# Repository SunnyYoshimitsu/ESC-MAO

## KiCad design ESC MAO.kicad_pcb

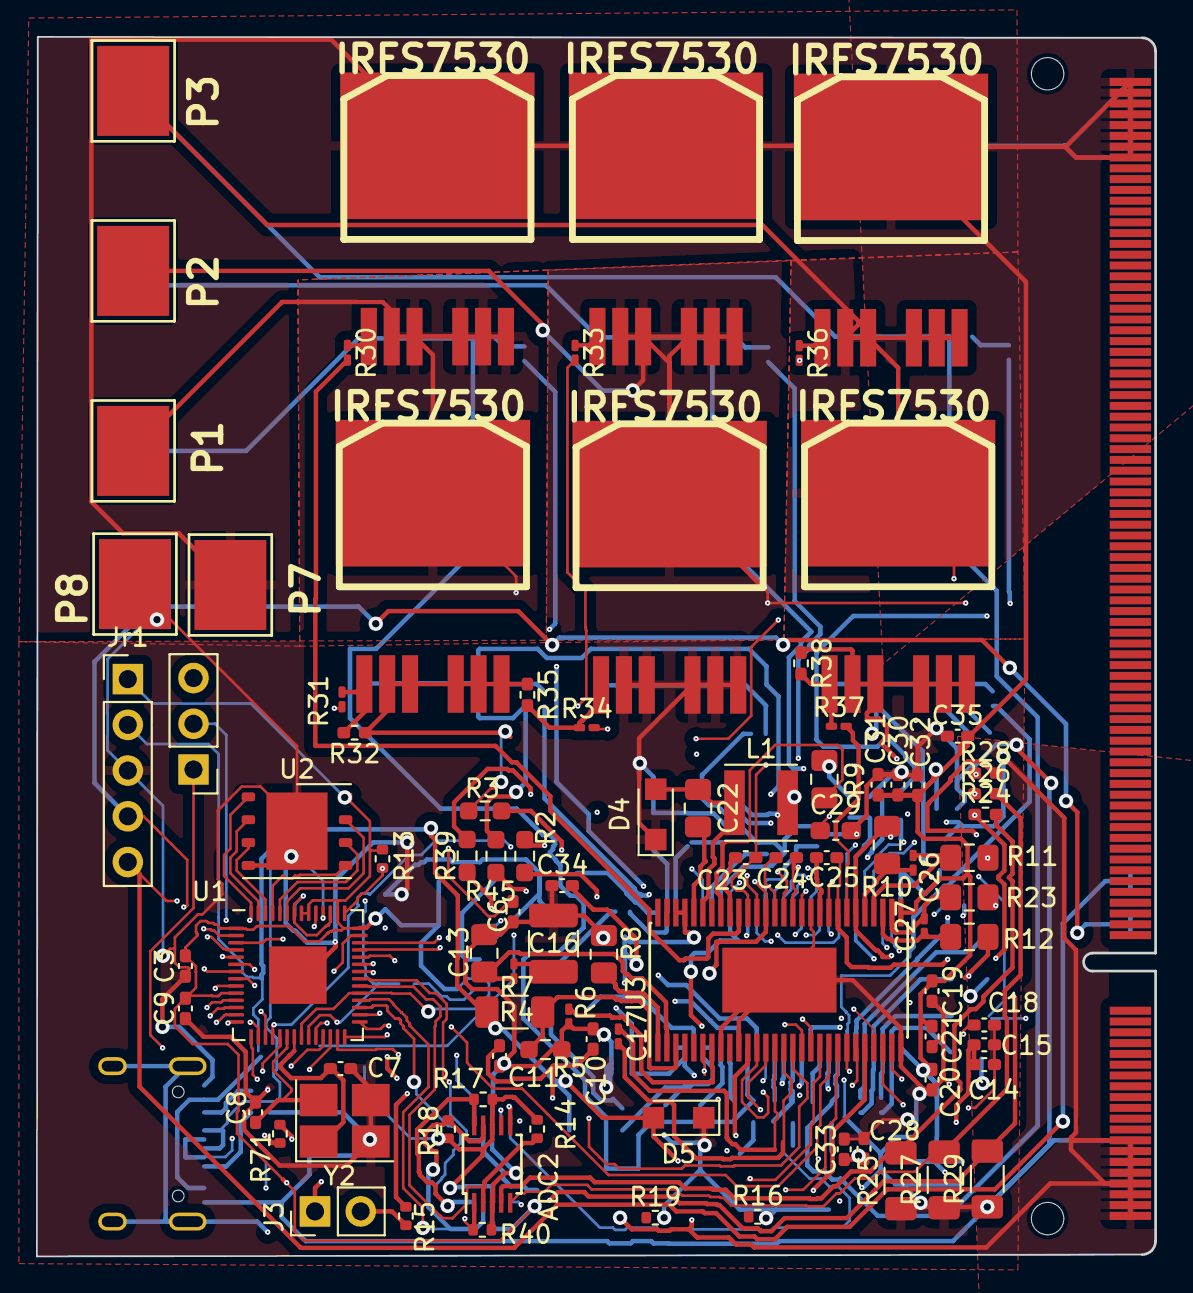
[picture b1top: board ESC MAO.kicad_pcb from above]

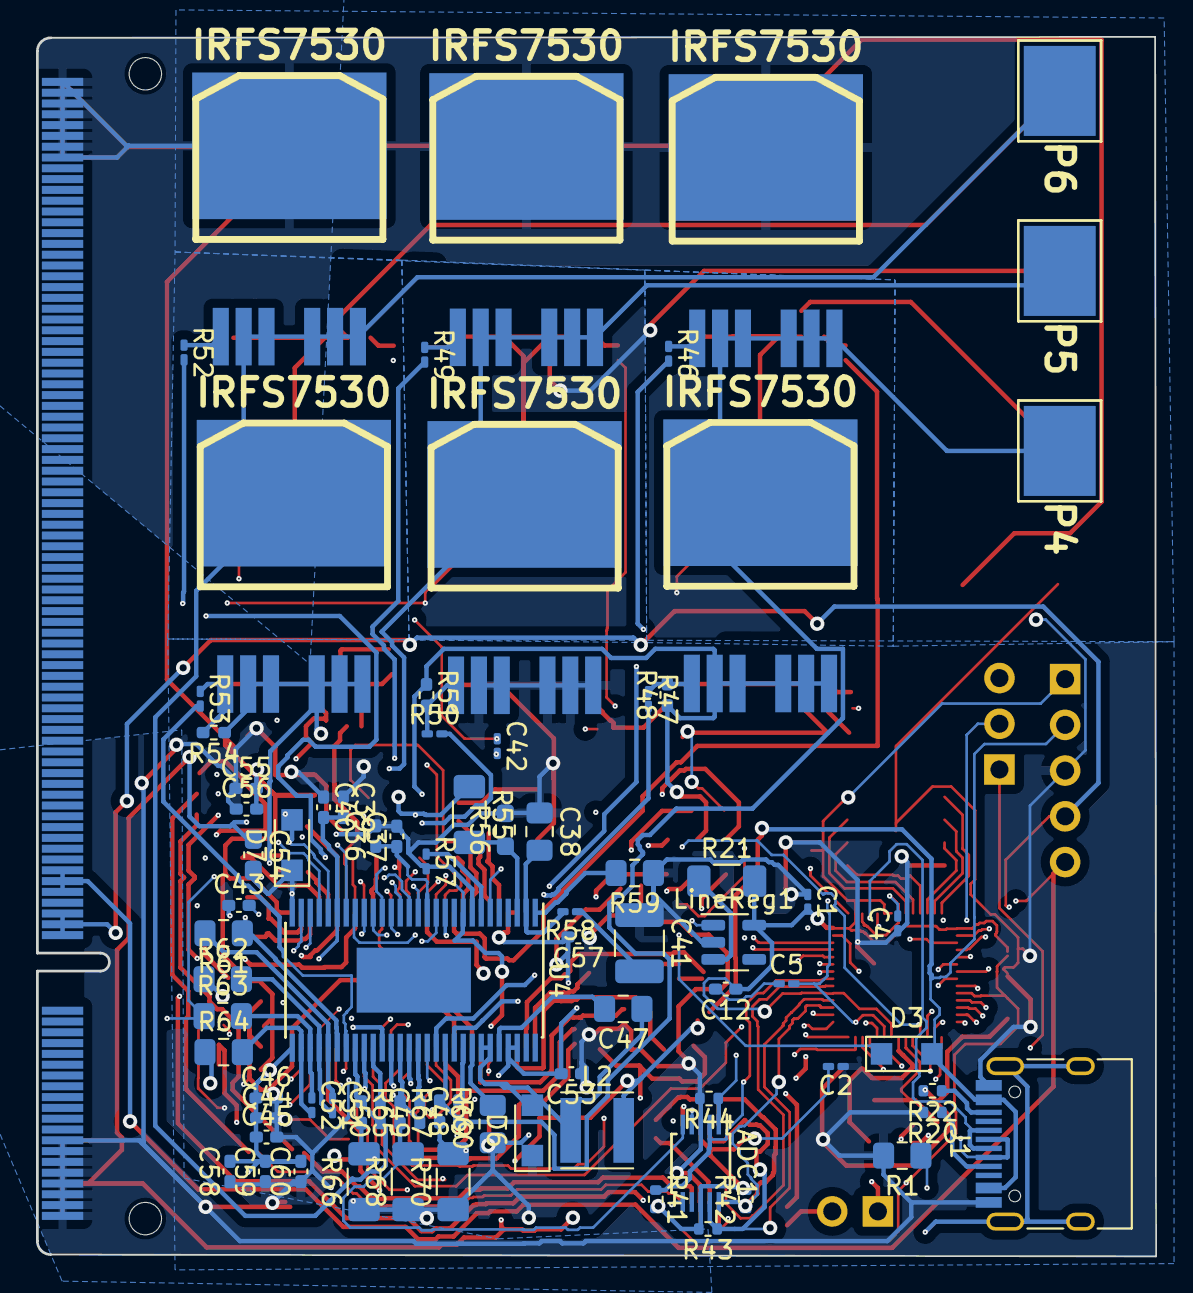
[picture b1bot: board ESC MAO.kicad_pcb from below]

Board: 4 copper layers, 62.1 x 67.8 mm, 171 parts (80 on the bottom side), 140 nets.

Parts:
ADC1, ADC2: ADS1015IDGS; TSSOP-10_3x3mm_P0.5mm
C1, C2, C4, C5: 100nF; C_0201_0603Metric_Pad0.64x0.40mm_HandSolder
C3, C6: 2.2uF; C_0402_1005Metric_Pad0.74x0.62mm_HandSolder
C7, C8: 15pF; C_0402_1005Metric_Pad0.74x0.62mm_HandSolder
C9, C12: 10uF; C_0402_1005Metric_Pad0.74x0.62mm_HandSolder
C10, C11, C14, C15, C18, C36, C37, C39, C40, C43: 2.2u; C_0402_1005Metric_Pad0.74x0.62mm_HandSolder
C13, C38: 120p; C_0805_2012Metric_Pad1.18x1.45mm_HandSolder
C16, C41: 6.8n; C_1210_3225Metric_Pad1.33x2.70mm_HandSolder
C17, C42: 22n; C_0201_0603Metric_Pad0.64x0.40mm_HandSolder
C19, C20, C21, C28, C30, C31, C33, C34, C44, C45, C46, C53, C55, C56, C58, C59: 10u,50V; C_0402_1005Metric_Pad0.74x0.62mm_HandSolder
C22, C47: 100n; C_0805_2012Metric_Pad1.18x1.45mm_HandSolder
C23, C24, C25, C48, C49, C50: 220n; C_0402_1005Metric_Pad0.74x0.62mm_HandSolder
C26, C27, C51, C52: 2.2n; C_0201_0603Metric_Pad0.64x0.40mm_HandSolder
C29, C54: 100u; C_0603_1608Metric_Pad1.08x0.95mm_HandSolder
C32, C57: 15u, 100v; C_0402_1005Metric_Pad0.74x0.62mm_HandSolder
C35, C60: 15u,100V; C_0402_1005Metric_Pad0.74x0.62mm_HandSolder
D3: MBR120VLSFT1G; Nexperia_CFP3_SOD-123W
D4, D6: DIODESCH; Nexperia_CFP3_SOD-123W
D5, D7: TVS 5V; Nexperia_CFP3_SOD-123W
J1: USB_C_Receptacle_USB2.0; USB_C_Receptacle_HRO_TYPE-C-31-M-12
J2: Conn_01x03_Pin; PinHeader_1x03_P2.54mm_Vertical
J3: Conn_01x02_Pin; PinHeader_1x02_P2.54mm_Vertical
Jr1: Conn_01x05_Pin; PinHeader_1x05_P2.54mm_Vertical
L1, L2: 22u; L_Vishay_IFSC-1515AH_4x4x1.8mm
LineReg1: TLV75733PDBV; SOT-23-5
P1, P4: MOTOR3; 1PAD_4x5mm
P2, P5: MOTOR2; 1PAD_4x5mm
P3, P6: MOTOR1; 1PAD_4x5mm
P7: IN+; 1PAD_4x5mm
P8: IN-; 1PAD_4x5mm
Q1, Q2, Q3, Q4, Q5, Q6, Q7, Q8, Q9, Q10, Q11, Q12: IRFS7530; D2PAK-7-GDS
R1, R9, R60: 1M; C_0805_2012Metric_Pad1.18x1.45mm_HandSolder
R2, R3, R39, R45: SHUNT; R_0603_1608Metric_Pad0.98x0.95mm_HandSolder
R4, R55: 18k; R_1206_3216Metric_Pad1.30x1.75mm_HandSolder
R5, R56: 3k3; R_0603_1608Metric_Pad0.98x0.95mm_HandSolder
R6, R57: 10k; R_0201_0603Metric_Pad0.64x0.40mm_HandSolder
R7, R58: 15k; R_0201_0603Metric_Pad0.64x0.40mm_HandSolder
R8, R59: 220k; C_0805_2012Metric_Pad1.18x1.45mm_HandSolder
R10, R11, R12, R23, R61, R62, R63, R64: 100R; C_0805_2012Metric_Pad1.18x1.45mm_HandSolder
R13, R14, R15, R17, R18, R20, R22, R40, R41, R42, R43, R44, R71: 5k; R_0402_1005Metric
R16, R19: 47.5k; R_0402_1005Metric
R21: 100k; R_1206_3216Metric_Pad1.30x1.75mm_HandSolder
R24, R26, R28, R32, R35, R38, R48, R51, R54, R65, R67, R69: 39k; R_0402_1005Metric_Pad0.72x0.64mm_HandSolder
R25, R27, R29, R66, R68, R70: 2k2; R_1206_3216Metric_Pad1.30x1.75mm_HandSolder
R30, R31, R33, R34, R36, R37, R46, R47, R49, R50, R52, R53: 4R7; R_0201_0603Metric_Pad0.64x0.40mm_HandSolder
SODIMM DDR2: SODIMM DDR2 EDGE; SODIMM_DDR2_EDGE
U1: RP2040; QFN-56-1EP_7x7mm_P0.4mm_EP3.2x3.2mm
U2: W25Q32JVZP; WSON-8-1EP_6x5mm_P1.27mm_EP3.4x4.3mm
U3, U4: DRV8302; HTSSOP-56-1EP_6.1x14mm_P0.5mm_EP3.61x6.35mm
Y2: 12MHz; Crystal_SMD_3225-4Pin_3.2x2.5mm_HandSoldering

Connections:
1BR_SO1: U1.38 (GPIO26_ADC0), U4.25 (SO1)
1BR_SO2: U1.39 (GPIO27_ADC1), U4.26 (SO2)
1DC_CAL: U1.15 (GPIO12), U4.12 (DC_CAL)
1H1: U1.17 (GPIO14), U4.17 (INH_A)
1H2: U1.27 (GPIO16), U4.19 (INH_B)
1H3: U1.29 (GPIO18), U4.21 (INH_C)
1L1: U1.18 (GPIO15), U4.18 (INL_A)
1L2: U1.28 (GPIO17), U4.20 (INL_B)
1L3: U1.30 (GPIO19), U4.22 (INL_C)
1SENS1: ADC1.4 (AIN0), R65.2, R66.2
1SENS2: ADC1.5 (AIN1), R67.2, R68.2
1SENS3: ADC1.6 (AIN2), R69.2, R70.2
+1V1: C4.2, C5.2, U1.23 (DVDD), U1.45 (VREG_VOUT), U1.50 (DVDD)
+3V3: ADC1.8 (VDD), ADC2.8 (VDD), C1.2, C2.2, C3.2, C9.2, C12.1, Jr1.1, LineReg1.5 (OUT), R13.2, R14.2, R17.2, R18.2, R21.2, R41.2, R42.2, R43.2, R71.2, U1.1 (IOVDD), U1.10 (IOVDD), U1.22 (IOVDD), U1.33 (IOVDD), U1.42 (IOVDD), U1.44 (VREG_IN), U1.48 (USB_VDD), U1.49 (IOVDD), U2.8 (VCC)
+5V: C29.1, C54.1, D3.2 (A), D5.2 (K), D7.2 (K), J1.A4 (VBUS), J1.A9 (VBUS), J1.B4 (VBUS), J1.B9 (VBUS), Jr1.2, L1.2, L2.2, R4.1, R55.1, SODIMM DDR2.1, SODIMM DDR2.3, SODIMM DDR2.5, SODIMM DDR2.9, SODIMM DDR2.11, SODIMM DDR2.13, SODIMM DDR2.15, SODIMM DDR2.e, U3.9 (M_OC), U3.24 (REF), U4.9 (M_OC), U4.24 (REF)
/MosfetDr1/H1_LOW: Q8.S, R45.2, R48.1, R51.1, R63.1, U4.44 (SL_A)
/MosfetDr1/H1_VS: C48.1, P4.1, Q7.S, Q8.D, R69.1, U4.46 (SH_A)
/MosfetDr1/H2_VS: C49.1, P5.1, Q9.S, Q10.D, R67.1, U4.41 (SH_B)
/MosfetDr1/H3_LOW: Q12.S, R39.1, R54.1, R61.1, U4.34 (SL_C)
/MosfetDr1/H3_VS: C50.1, P6.1, Q11.S, Q12.D, R65.1, U4.36 (SH_C)
/MosfetDr1/M_H1: R46.2, U4.47 (GH_A)
/MosfetDr1/M_H2: R49.2, U4.42 (GH_B)
/MosfetDr1/M_H3: R52.2, U4.37 (GH_C)
/MosfetDr1/M_L1: R47.2, U4.45 (GL_A)
/MosfetDr1/M_L2: R50.2, U4.40 (GL_B)
/MosfetDr1/M_L3: R53.2, U4.35 (GL_C)
/MosfetDr/H1_LOW: Q2.S, R3.2, R12.1, R32.1, R35.1, U3.44 (SL_A)
/MosfetDr/H1_VS: C23.1, P1.1, Q1.S, Q2.D, R28.1, U3.46 (SH_A)
/MosfetDr/H2_VS: C24.1, P2.1, Q3.S, Q4.D, R26.1, U3.41 (SH_B)
/MosfetDr/H3_LOW: Q6.S, R2.1, R10.1, R38.1, U3.34 (SL_C)
/MosfetDr/H3_VS: C25.1, P3.1, Q5.S, Q6.D, R24.1, U3.36 (SH_C)
/MosfetDr/M_H1: R30.2, U3.47 (GH_A)
/MosfetDr/M_H2: R33.2, U3.42 (GH_B)
/MosfetDr/M_H3: R36.2, U3.37 (GH_C)
/MosfetDr/M_L1: R31.2, U3.45 (GL_A)
/MosfetDr/M_L2: R34.2, U3.40 (GL_B)
/MosfetDr/M_L3: R37.2, U3.35 (GL_C)
/PowerMana1/SH1_B: R39.2, R62.1
/PowerMana1/SH2_B: R45.1, R64.1
/PowerMana/SH1_B: R2.2, R11.1
/PowerMana/SH2_B: R3.1, R23.1
ADCs0: ADC2.1 (ADDR), R40.1, U1.12 (GPIO9)
ADCs1: ADC1.1 (ADDR), R44.1, U1.13 (GPIO10)
BR_SO1: U1.40 (GPIO28_ADC2), U3.25 (SO1)
BR_SO2: U1.41 (GPIO29_ADC3), U3.26 (SO2)
DC_CAL: U1.3 (GPIO1), U3.12 (DC_CAL)
En_GATE: U1.4 (GPIO2), U3.16 (EN_GATE)
En_GATE1: U1.16 (GPIO13), U4.16 (EN_GATE)
GND: ADC1.3 (GND), ADC2.3 (GND), C1.1, C2.1, C3.1, C4.1, C5.1, C6.1, C7.1, C8.1, C9.1, C10.2, C11.2, C12.2, C13.1, C14.1, C15.1, C16.1, C18.1, C19.2, C20.2, C21.2, C28.1, C29.2, C30.1, C31.1, C32.1, C33.1, C34.1, C35.1, C36.2, C37.2, C38.1, C39.1, C40.1, C41.1, C43.1, C44.2, C45.2, C46.2, C53.1, C54.2, C55.1, C56.1, C57.1, C58.1, C59.1, C60.1, D4.1 (A), D5.1 (A), D6.1 (A), D7.1 (A), J1.A1 (GND), J1.A12 (GND), J1.B1 (GND), J1.B12 (GND), Jr1.3, LineReg1.2 (GND), P8.1, Q4.S, Q10.S, R1.2, R5.2, R6.2, R8.1, R9.1, R16.2, R19.2, R20.2, R22.2, R25.1, R27.1, R29.1, R40.2, R44.2, R56.2, R57.2, R59.1, R60.1, R66.1, R68.1, R70.1, SODIMM DDR2.2, SODIMM DDR2.4, SODIMM DDR2.6, SODIMM DDR2.8, SODIMM DDR2.10, SODIMM DDR2.12, SODIMM DDR2.14, SODIMM DDR2.16, U1.57 (GND), U2.4 (GND), U2.9 (EP), U3.8 (M_PWM), U3.10 (GAIN), U3.28 (AGND), U3.39 (SL_B), U3.57 (GND(POWER_PAD)), U4.8 (M_PWM), U4.10 (GAIN), U4.28 (AGND), U4.39 (SL_B), U4.57 (GND(POWER_PAD)), Y2.2, Y2.3
H1: U1.5 (GPIO3), U3.17 (INH_A)
H2: U1.7 (GPIO5), U3.19 (INH_B)
H3: U1.9 (GPIO7), U3.21 (INH_C)
K7: LineReg1.3 (EN), R21.1
L1: U1.6 (GPIO4), U3.18 (INL_A)
L2: U1.8 (GPIO6), U3.20 (INL_B)
L3: U1.11 (GPIO8), U3.22 (INL_C)
unnamed: C16.2, R7.1
unnamed: C41.2, R58.1
unnamed: C22.1, D4.2 (K), L1.1, U3.50 (PH), U3.51 (PH)
unnamed: C47.1, D6.2 (K), L2.1, U4.50 (PH), U4.51 (PH)
unnamed: J1.A5 (CC1), R20.1
unnamed: J1.B5 (CC2), R22.1
unnamed: J1.S1 (SHIELD), R1.1
unnamed: J2.1, U1.25 (SWD)
unnamed: J2.2, U1.24 (SWCLK)
unnamed: J2.3, U1.19 (TESTEN)
unnamed: J3.1, R71.1, U1.26 (RUN)
unnamed: J3.2, R15.1
unnamed: Q1.G, R30.1
unnamed: Q2.G, R31.1, R32.2
unnamed: Q3.G, R33.1
unnamed: Q4.G, R34.1, R35.2
unnamed: Q5.G, R36.1
unnamed: Q6.G, R37.1, R38.2
unnamed: Q7.G, R46.1
unnamed: Q8.G, R47.1, R48.2
unnamed: Q9.G, R49.1
unnamed: Q10.G, R50.1, R51.2
unnamed: Q11.G, R52.1
unnamed: Q12.G, R53.1, R54.2
unnamed: C6.2, R13.1, U1.43 (ADC_AVDD)
unnamed: U1.52 (QSPI_SCLK), U2.6 (CLK)
unnamed: U1.53 (QSPI_SD0), U2.5 (DI(IO0))
unnamed: U1.55 (QSPI_SD1), U2.2 (DO(IO1))
unnamed: U1.54 (QSPI_SD2), U2.3 (IO2)
unnamed: U1.51 (QSPI_SD3), U2.7 (IO3)
unnamed: R15.2, U1.56 (QSPI_SS), U2.1 (~CS)
unnamed: J1.A6 (D+), J1.B6 (D+), U1.46 (USB_DM)
unnamed: J1.A7 (D-), J1.B7 (D-), U1.47 (USB_DP)
unnamed: C8.2, U1.20 (XIN), Y2.4
unnamed: C7.2, U1.21 (XOUT), Y2.1
unnamed: C18.2, U3.27 (AVDD)
unnamed: R9.2, U3.49 (BIAS)
unnamed: C23.2, U3.48 (BST_A)
unnamed: C24.2, U3.43 (BST_B)
unnamed: C22.2, U3.52 (BST_BK)
unnamed: C25.2, U3.38 (BST_C)
unnamed: C13.2, R7.2, U3.2 (COMP)
unnamed: C17.1, U3.14 (CP1)
unnamed: C17.2, U3.15 (CP2)
unnamed: R6.1, U3.7 (DTC)
unnamed: C14.2, C15.2, U3.11 (OC_ADJ), U3.23 (DVDD)
unnamed: C10.1, C11.1, U3.13 (GVDD)
unnamed: R8.2, U3.1 (RT_CLK)
unnamed: C26.1, R10.2, U3.33 (SN1)
unnamed: C27.1, R12.2, U3.31 (SN2)
unnamed: C26.2, R11.2, U3.32 (SP1)
unnamed: C27.2, R23.2, U3.30 (SP2)
unnamed: R4.2, R5.1, U3.3 (VSENSE)
unnamed: C43.2, U4.27 (AVDD)
unnamed: R60.2, U4.49 (BIAS)
unnamed: C48.2, U4.48 (BST_A)
unnamed: C49.2, U4.43 (BST_B)
unnamed: C47.2, U4.52 (BST_BK)
unnamed: C50.2, U4.38 (BST_C)
unnamed: C38.2, R58.2, U4.2 (COMP)
unnamed: C42.1, U4.14 (CP1)
unnamed: C42.2, U4.15 (CP2)
unnamed: R57.1, U4.7 (DTC)
unnamed: C39.2, C40.2, U4.11 (OC_ADJ), U4.23 (DVDD)
unnamed: C36.1, C37.1, U4.13 (GVDD)
unnamed: R59.2, U4.1 (RT_CLK)
unnamed: C51.1, R61.2, U4.33 (SN1)
unnamed: C52.1, R63.2, U4.31 (SN2)
unnamed: C51.2, R62.2, U4.32 (SP1)
unnamed: C52.2, R64.2, U4.30 (SP2)
unnamed: R55.2, R56.1, U4.3 (VSENSE)
Rx: Jr1.5, SODIMM DDR2.50, SODIMM DDR2.52, SODIMM DDR2.54, U1.37 (GPIO25)
SCL: ADC1.10 (SCL), ADC2.10 (SCL), R17.1, R42.1, U1.31 (GPIO20)
SDA: ADC1.9 (SDA), ADC2.9 (SDA), R18.1, R43.1, U1.32 (GPIO21)
SENS1: ADC2.4 (AIN0), R24.2, R25.2
SENS2: ADC2.5 (AIN1), R26.2, R27.2
SENS3: ADC2.6 (AIN2), R28.2, R29.2
Tx: Jr1.4, SODIMM DDR2.42, SODIMM DDR2.44, SODIMM DDR2.46, U1.36 (GPIO24)
VBus: D3.1 (K), LineReg1.1 (IN)
V_SUPPLY: C19.1, C20.1, C21.1, C28.2, C30.2, C31.2, C32.2, C33.2, C34.2, C35.2, C44.1, C45.1, C46.1, C53.2, C55.2, C56.2, C57.2, C58.2, C59.2, C60.2, P7.1, Q1.D, Q3.D, Q5.D, Q7.D, Q9.D, Q11.D, SODIMM DDR2.185, SODIMM DDR2.186, SODIMM DDR2.187, SODIMM DDR2.188, SODIMM DDR2.189, SODIMM DDR2.190, SODIMM DDR2.191, SODIMM DDR2.192, SODIMM DDR2.193, SODIMM DDR2.194, SODIMM DDR2.195, SODIMM DDR2.196, SODIMM DDR2.197, SODIMM DDR2.198, SODIMM DDR2.199, SODIMM DDR2.200, U3.29 (PVDD1), U3.53 (PVDD2), U3.54 (PVDD2), U4.29 (PVDD1), U4.53 (PVDD2), U4.54 (PVDD2)
rdy0: ADC2.2 (ALERT/RDY), R14.1, U1.34 (GPIO22)
rdy1: ADC1.2 (ALERT/RDY), R41.1, U1.35 (GPIO23)
~FAULT: U1.2 (GPIO0), U3.6 (FAULT)
~FAULT1: U1.14 (GPIO11), U4.6 (FAULT)
